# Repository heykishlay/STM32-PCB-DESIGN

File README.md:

# STM32 Custom Development Board

A custom STM32F103 development board designed in KiCad with USB connectivity, onboard power regulation, GPIO expansion, and SWD programming support.

---

## Overview

This project focuses on designing a custom STM32-based PCB while learning practical embedded hardware design concepts and PCB development workflow.

The board includes:

* STM32F103C8x6 microcontroller
* Micro USB interface
* AMS1117 3.3V regulator
* Crystal oscillator
* Decoupling capacitor network
* SWD programming interface
* GPIO expansion headers
* Mounting holes

---

## Features

* Custom STM32F103 PCB design
* USB power and communication support
* Onboard 3.3V voltage regulation
* SWD debugging/programming header
* External crystal support
* GPIO breakout headers
* Designed in KiCad

---

## Hardware Used

| Component   | Description                 |
| ----------- | --------------------------- |
| MCU         | STM32F103C8x6               |
| Regulator   | AMS1117-3.3                 |
| USB         | Micro USB                   |
| Clock       | External Crystal Oscillator |
| Programming | SWD Interface               |

---

## Project Workflow

1. Schematic design
2. Footprint assignment
3. PCB layout generation
4. Component placement
5. Routing
6. Design rule checking
7. PCB preparation for manufacturing
---

## Tools Used

* KiCad
* STM32 ecosystem
* GitHub

---

## Author

Kishlay Dwivedi

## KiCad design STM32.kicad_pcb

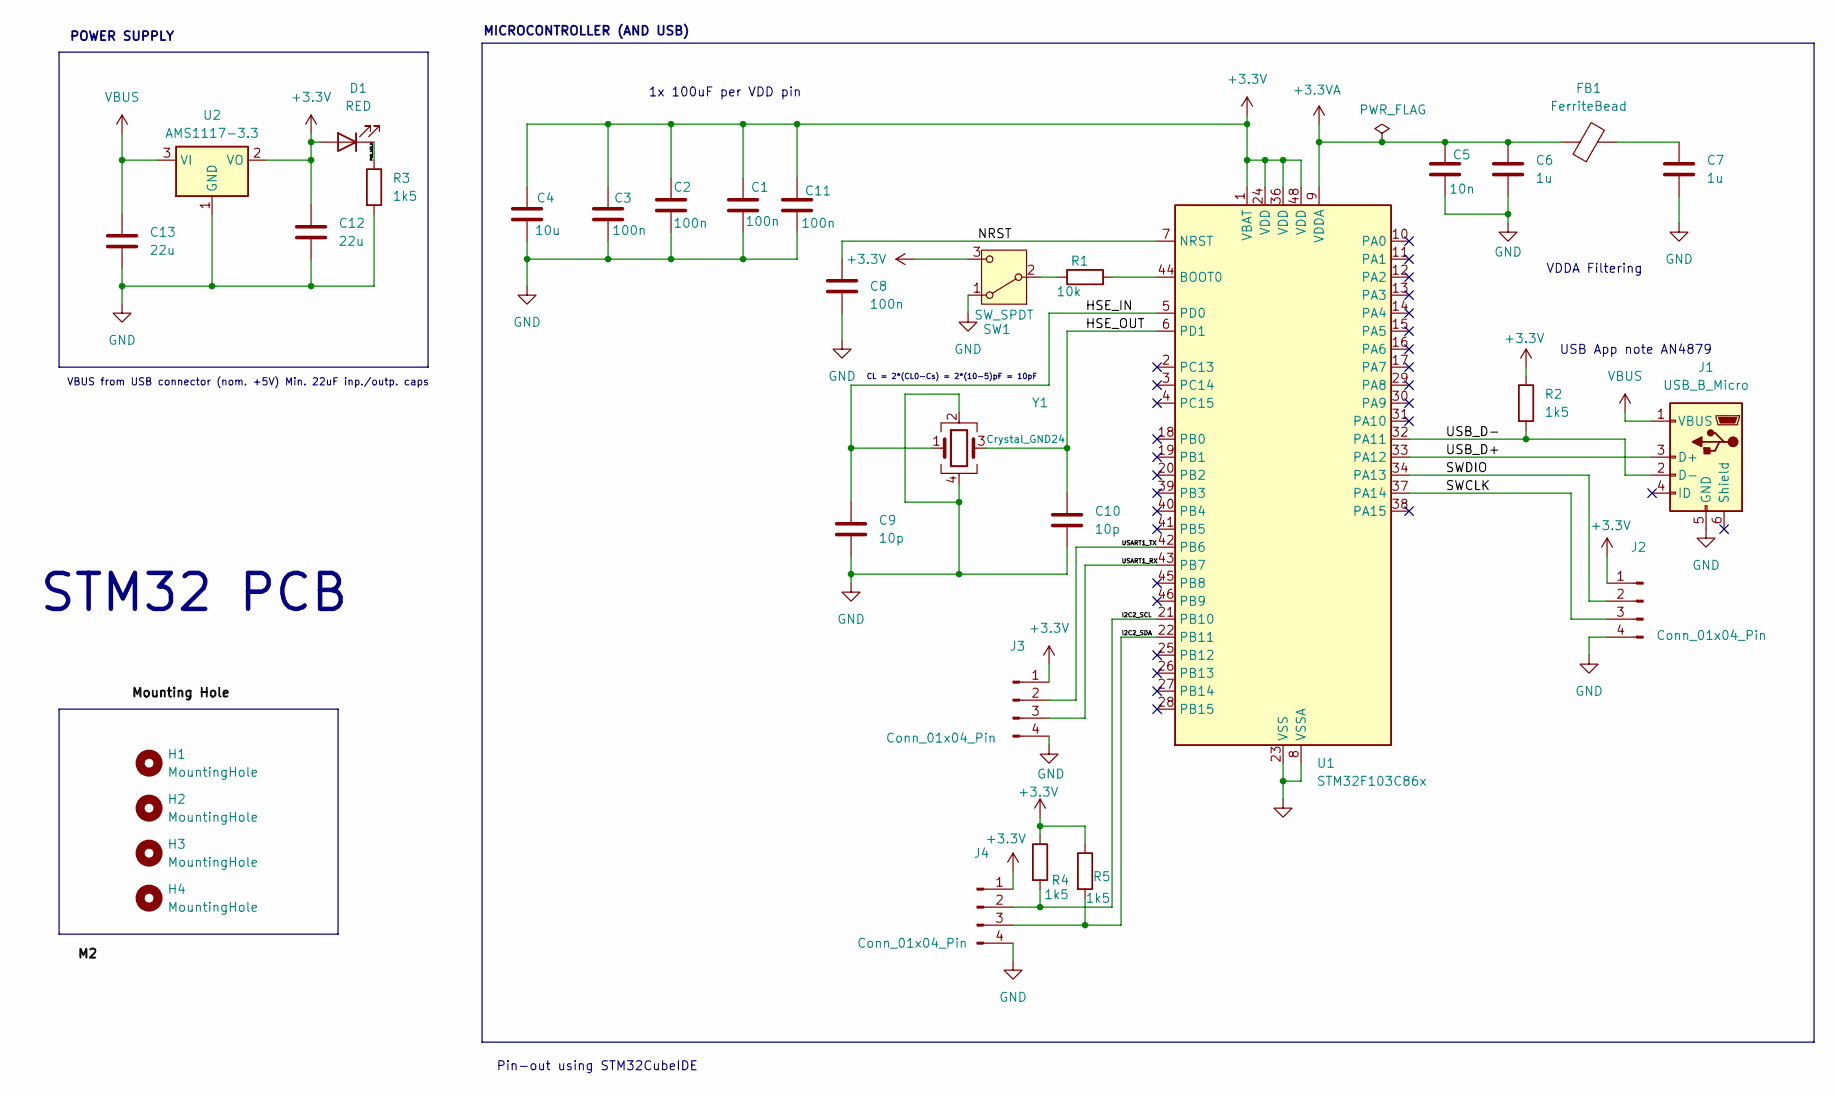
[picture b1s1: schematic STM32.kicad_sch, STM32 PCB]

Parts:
C1, C2, C3, C11: 100n; C_01005_0402Metric
C4: 10u; C_0603_1608Metric
C5: 10n; C_0402_1005Metric
C6, C7: 1u; C_0402_1005Metric
C8: 100n; C_0402_1005Metric
C9, C10: 10p; C_0402_1005Metric
C12, C13: 22u; C_0805_2012Metric
D1: RED; LED_0603_1608Metric_Pad1.05x0.95mm_HandSolder
FB1: FerriteBead; L_0603_1608Metric_Pad1.05x0.95mm_HandSolder
H1, H2, H3, H4: MountingHole; MountingHole_2.2mm_M2
J1: USB_B_Micro; USB_Micro-B_Wuerth_614105150721_Vertical
J2, J3, J4: Conn_01x04_Pin; PinHeader_1x04_P2.54mm_Vertical
R1: 10k; R_0402_1005Metric
R2, R3, R4, R5: 1k5; R_0402_1005Metric
SW1: SW_SPDT; SW_E-Switch_EG1224_SPDT_Angled
U1: STM32F103C86x; LQFP-48_7x7mm_P0.5mm
U2: AMS1117-3.3; SOT-223-3_TabPin2
Y1: Crystal_GND24; Crystal_SMD_3225-4Pin_3.2x2.5mm

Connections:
+3.3V: C1.1, C2.1, C3.1, C4.1, C11.1, C12.1, D1.2 (A), J2.1, J3.1, J4.1, R2.1, R4.1, R5.1, SW1.3 (C), U1.1 (VBAT), U1.24 (VDD), U1.36 (VDD), U1.48 (VDD), U2.2 (VO)
+3.3VA: C5.1, C6.1, FB1.1, U1.9 (VDDA)
/HSE_IN: C9.1, U1.5 (PD0), Y1.1
/HSE_OUT: C10.1, U1.6 (PD1), Y1.3
/I2C2_SCL: J4.2, R4.2, U1.21 (PB10)
/I2C2_SDA: J4.3, R5.2, U1.22 (PB11)
/NRST: C8.1, U1.7 (NRST)
/PWR_LED_K: D1.1 (K), R3.1
/SWCLK: J2.3, U1.37 (PA14)
/SWDIO: J2.2, U1.34 (PA13)
/USART1_RX: J3.3, U1.43 (PB7)
/USART1_TX: J3.2, U1.42 (PB6)
/USB_D+: J1.3 (D+), U1.33 (PA12)
/USB_D-: J1.2 (D-), R2.2, U1.32 (PA11)
GND: C1.2, C2.2, C3.2, C4.2, C5.2, C6.2, C7.2, C8.2, C9.2, C10.2, C11.2, C12.2, C13.2, J1.5 (GND), J2.4, J3.4, J4.4, R3.2, SW1.1 (A), U2.1 (GND), Y1.2, Y1.4
unnamed: C7.1, FB1.2
unnamed: R1.1, SW1.2 (B)
unnamed: R1.2, U1.44 (BOOT0)
VBUS: C13.1, J1.1 (VBUS), U2.3 (VI)
~: U1.8 (VSSA), U1.23 (VSS), U1.35 (VSS), U1.47 (VSS)

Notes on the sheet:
USB App note AN4879
1x 100uF per VDD pin
Pin-out using STM32CubeIDE
POWER SUPPLY
CL = 2*(CL0-Cs) = 2*(10-5)pF = 10pF
STM32 PCB
MICROCONTROLLER (AND USB)
VDDA Filtering
VBUS from USB connector (nom. +5V) Min. 22uF inp./outp. caps

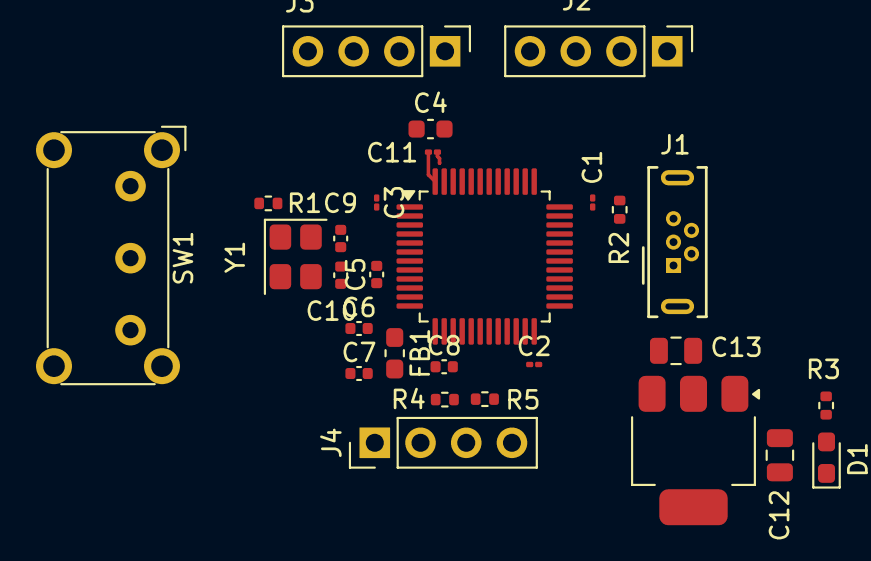
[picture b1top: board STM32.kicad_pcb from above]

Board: 2 copper layers, 32 parts (0 on the bottom side), 20 nets.
